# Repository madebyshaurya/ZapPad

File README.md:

# ZapPad

## Description
ZapPad is meant to be a programmable macropad which can do anything, you can display anything on the OLED screen, make the rotary encoder change something, and same for the keys. But currently it is made to be a media controller which can control your volume with the knob and more as you can see below.

## Visuals

## BOM
| Designator                                | Footprint                                           | Quantity | Value                |
|-------------------------------------------|-----------------------------------------------------|----------|----------------------|
| D1, D2, D3, D4, D5, D6, D7, D8, D9         | Diode_DO-35                                         | 9        | Diode                |
| J1                                        | SSD1306-0.91-OLED-4pin-128x32                       | 1        | Conn_01x04_Pin       |
| S1, S2, S3, S4, S5, S6, S7, S8, S9         | MX_PCB_1.00u                                        | 9        | Keyswitch            |
| SW1                                       | RotaryEncoder_Alps_EC11E-Switch_Vertical_H20mm      | 1        | RotaryEncoder_Switch |
| U1                                        | XIAO-RP2040-DIP                                     | 1        | XIAO-RP2040-DIP      |

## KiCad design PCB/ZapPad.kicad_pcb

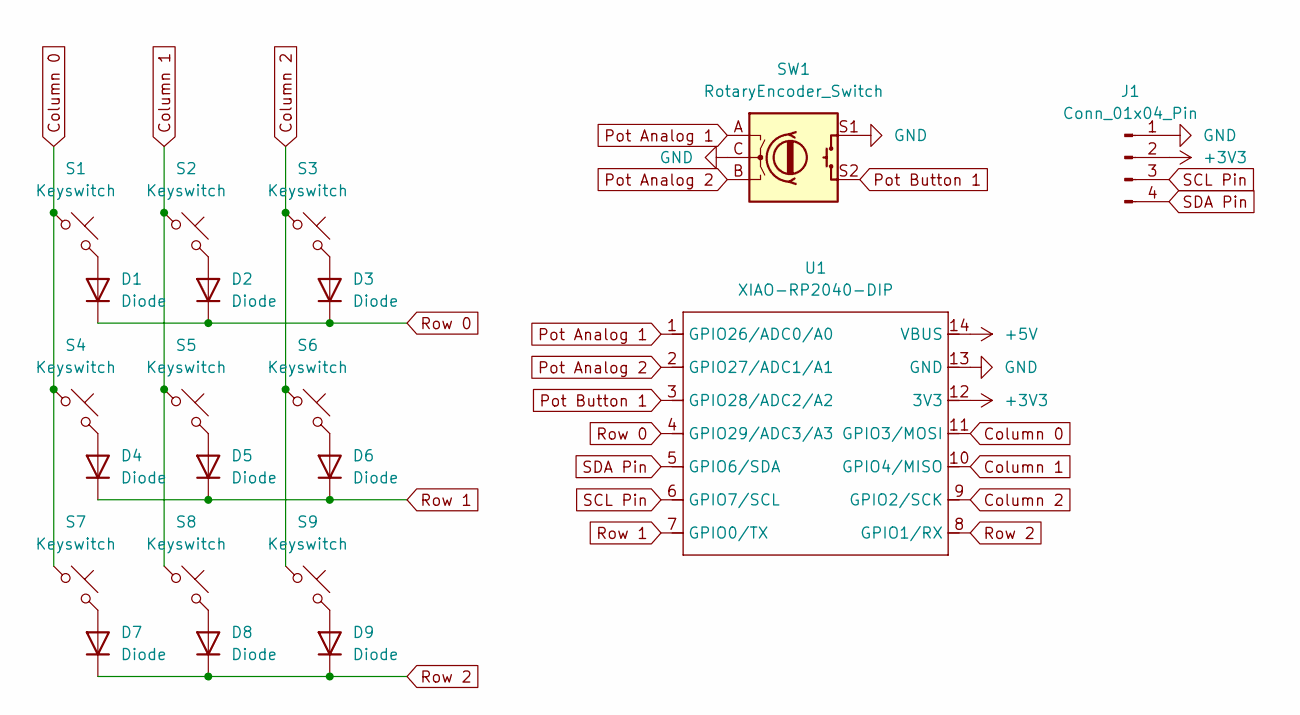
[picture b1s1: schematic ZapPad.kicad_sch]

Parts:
D1, D2, D3, D4, D5, D6, D7, D8, D9: Diode; Diode_DO-35
J1: Conn_01x04_Pin; SSD1306-0.91-OLED-4pin-128x32
S1, S2, S3, S4, S5, S6, S7, S8, S9: Keyswitch; MX_PCB_1.00u
SW1: RotaryEncoder_Switch; RotaryEncoder_Alps_EC11E-Switch_Vertical_H20mm
U1: XIAO-RP2040-DIP

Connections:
+3V3: J1.2, U1.12 (3V3)
+5V: U1.14 (VBUS)
Column 0: S1.1, S4.1, S7.1, U1.11 (GPIO3/MOSI)
Column 1: S2.1, S5.1, S8.1, U1.10 (GPIO4/MISO)
Column 2: S3.1, S6.1, S9.1, U1.9 (GPIO2/SCK)
GND: J1.1, SW1.C, SW1.S1, U1.13 (GND)
unnamed: D1.2 (A), S1.2
unnamed: D2.2 (A), S2.2
unnamed: D3.2 (A), S3.2
unnamed: D4.2 (A), S4.2
unnamed: D5.2 (A), S5.2
unnamed: D6.2 (A), S6.2
unnamed: D7.2 (A), S7.2
unnamed: D8.2 (A), S8.2
unnamed: D9.2 (A), S9.2
Pot Analog 1: SW1.A, U1.1 (GPIO26/ADC0/A0)
Pot Analog 2: SW1.B, U1.2 (GPIO27/ADC1/A1)
Pot Button 1: SW1.S2, U1.3 (GPIO28/ADC2/A2)
Row 0: D1.1 (K), D2.1 (K), D3.1 (K), U1.4 (GPIO29/ADC3/A3)
Row 1: D4.1 (K), D5.1 (K), D6.1 (K), U1.7 (GPIO0/TX)
Row 2: D7.1 (K), D8.1 (K), D9.1 (K), U1.8 (GPIO1/RX)
SCL Pin: J1.3, U1.6 (GPIO7/SCL)
SDA Pin: J1.4, U1.5 (GPIO6/SDA)

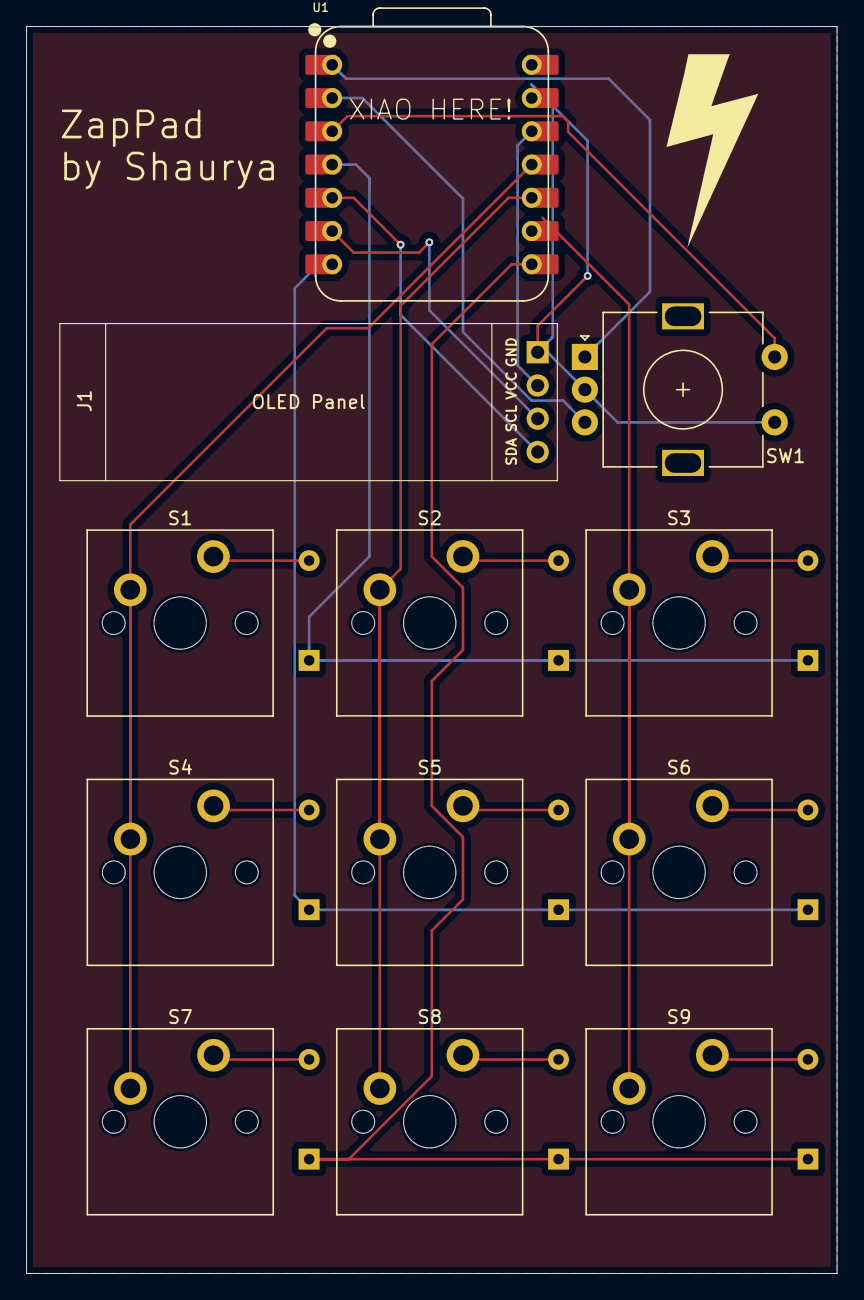
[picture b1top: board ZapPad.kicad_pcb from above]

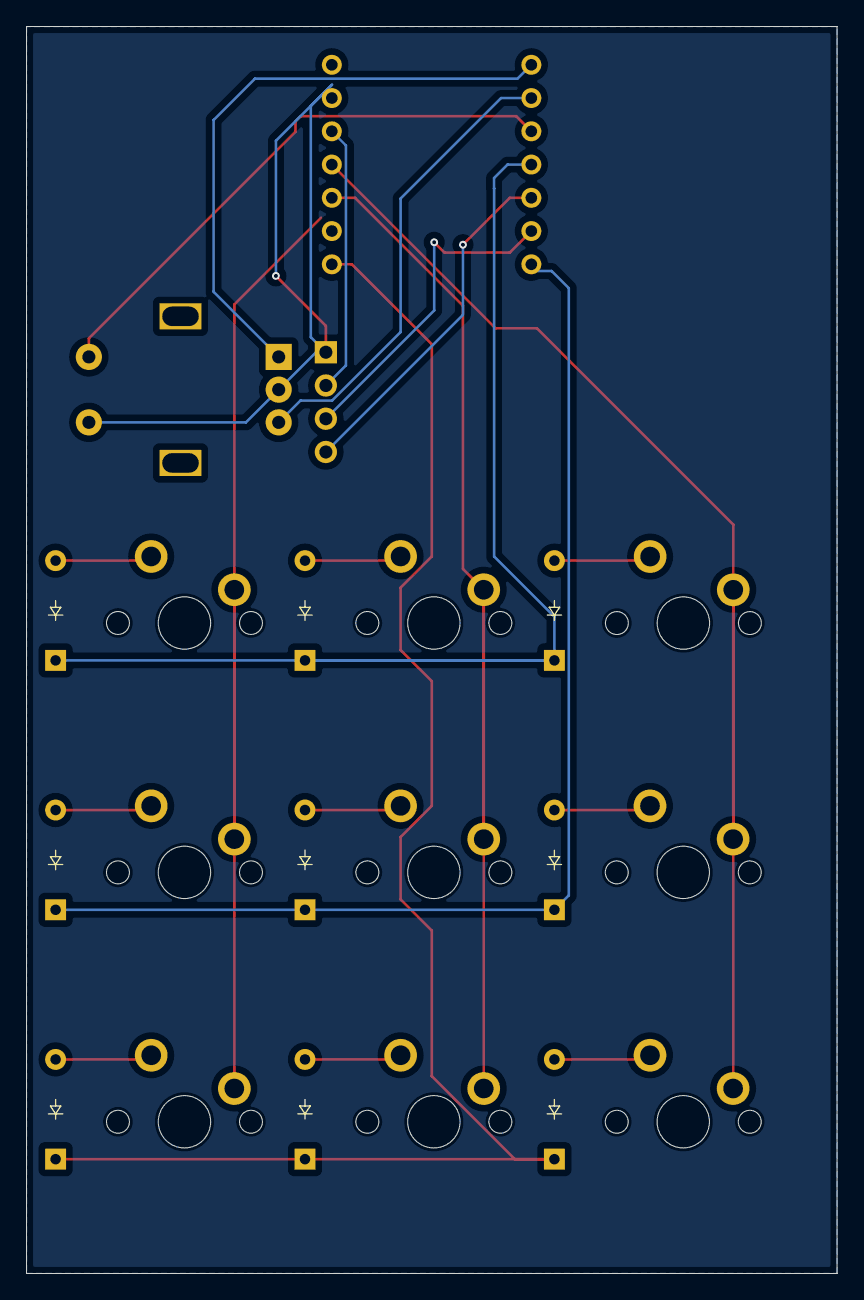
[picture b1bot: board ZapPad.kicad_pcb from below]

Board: 2 copper layers, 61.9 x 95.2 mm, 21 parts (9 on the bottom side), 22 nets.

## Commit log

2025-06-01 added all files
2025-06-01 ready to submit
2025-06-07 Added description
2025-06-12 updated case
2025-06-12 Added more images. and updated few
